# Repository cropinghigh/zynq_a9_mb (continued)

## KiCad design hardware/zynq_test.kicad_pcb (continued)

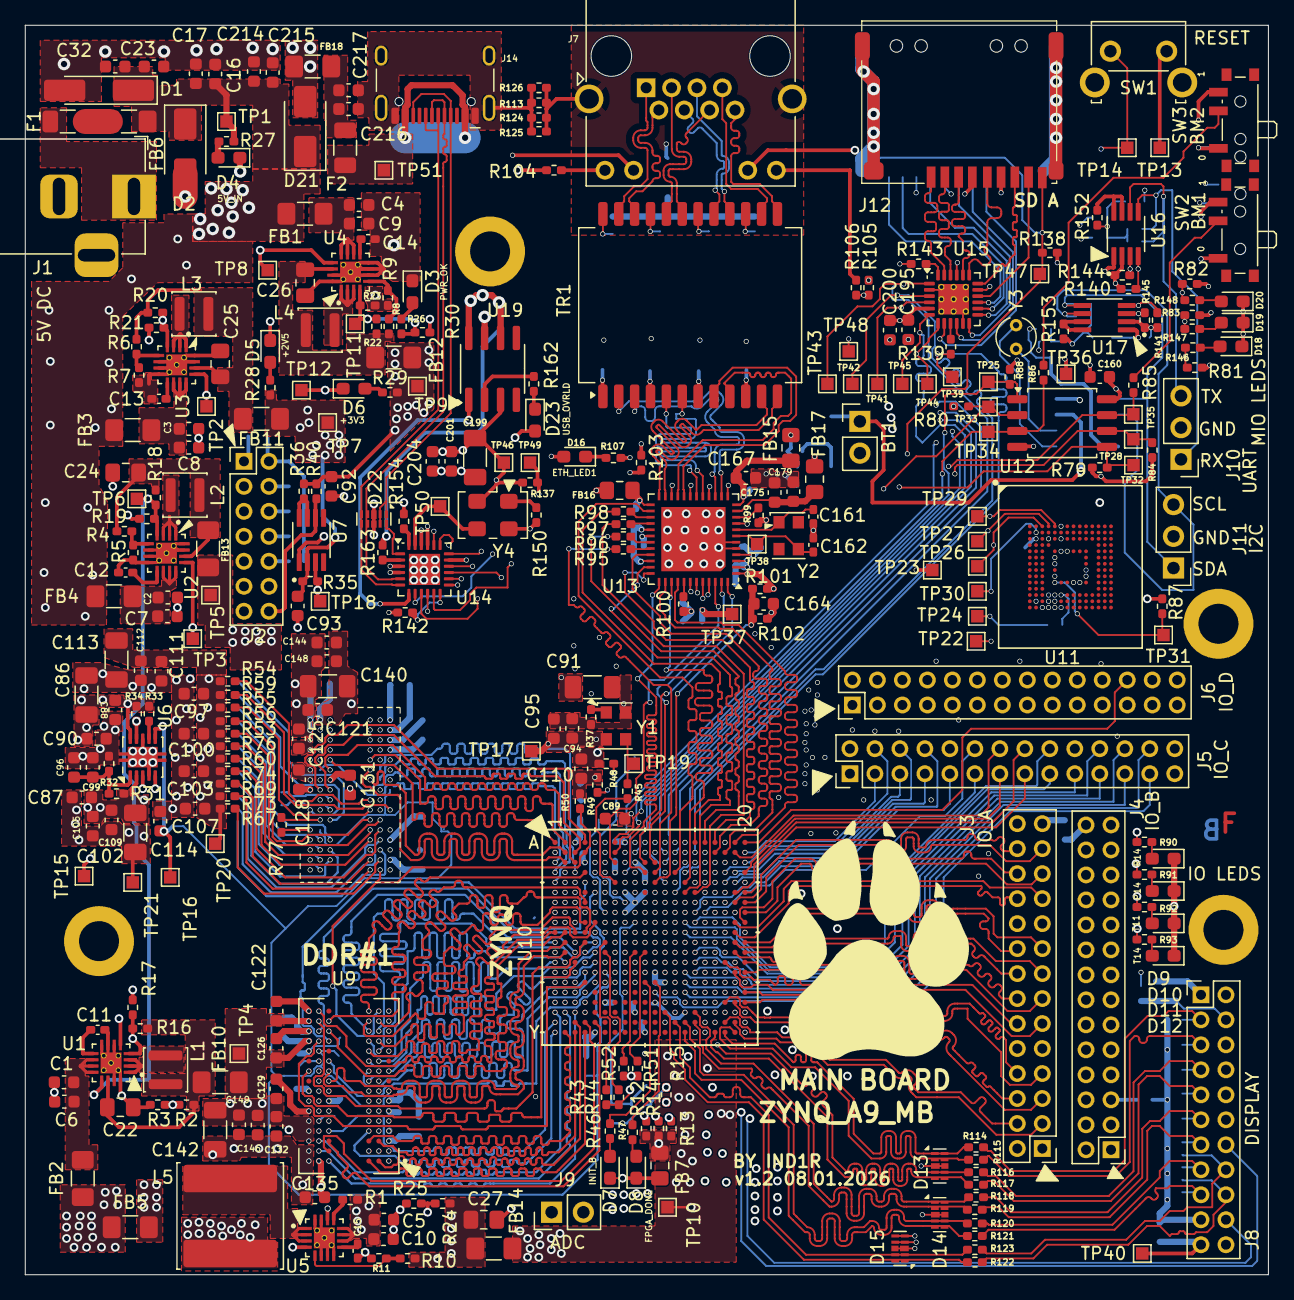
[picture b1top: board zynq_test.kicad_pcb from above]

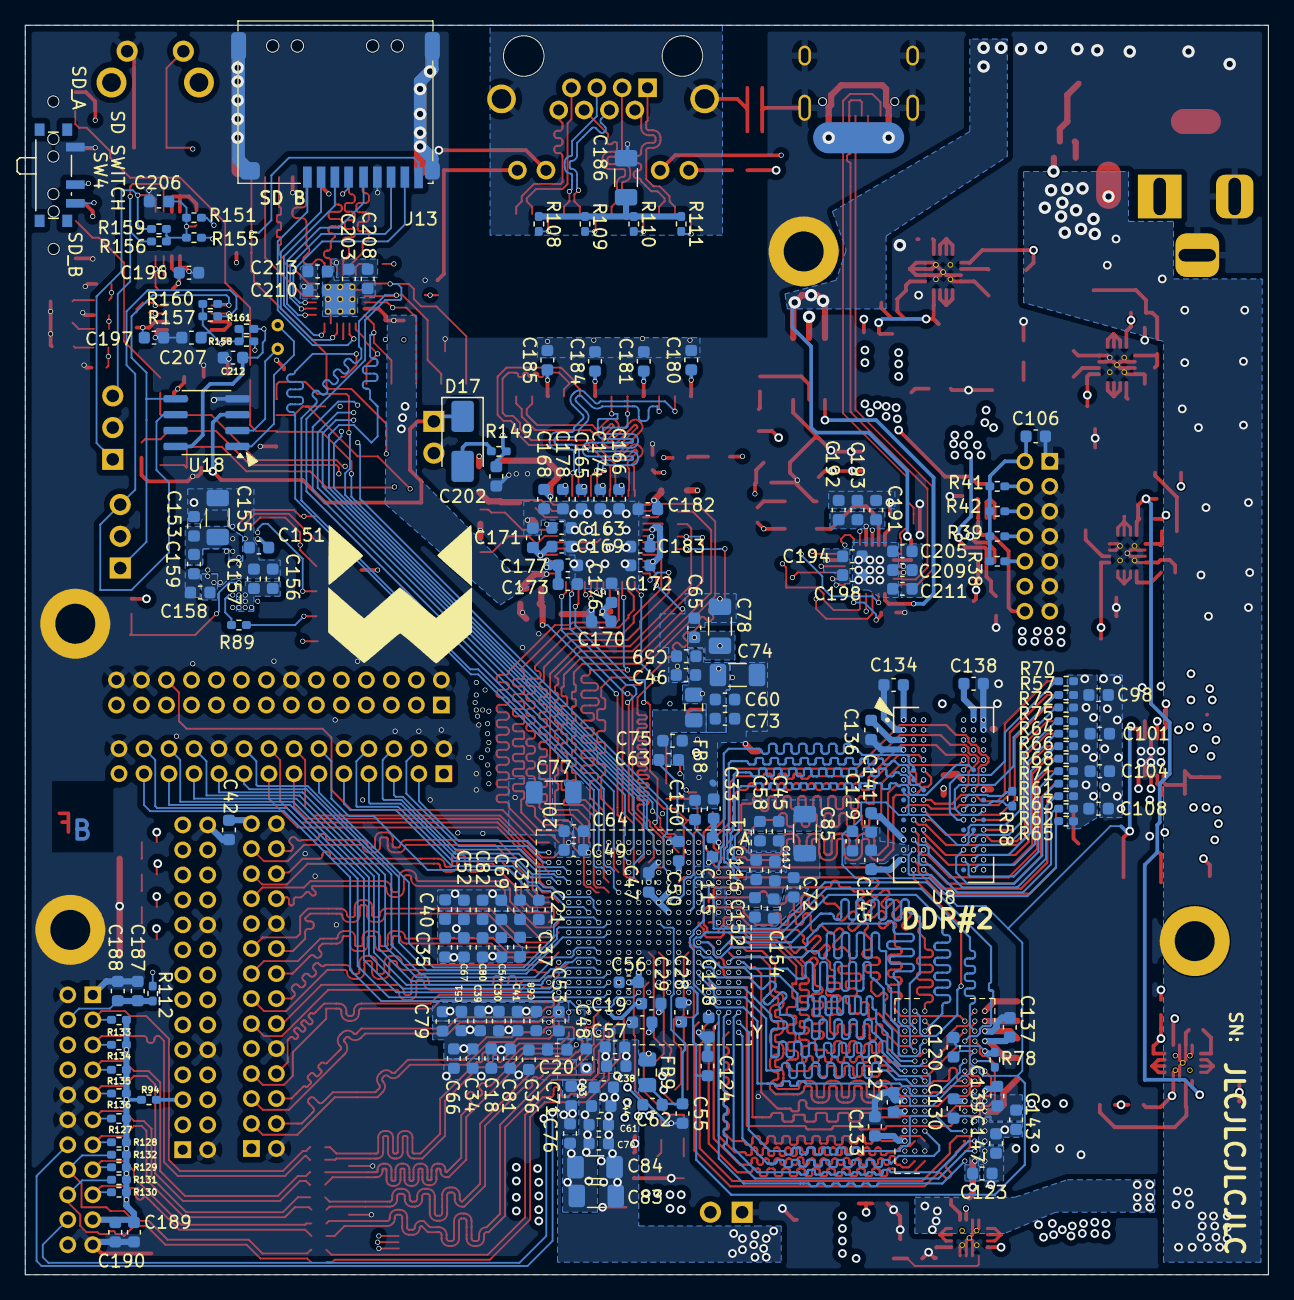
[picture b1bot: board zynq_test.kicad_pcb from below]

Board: 6 copper layers, 99.5 x 100.0 mm, 526 parts (189 on the bottom side), 412 nets.

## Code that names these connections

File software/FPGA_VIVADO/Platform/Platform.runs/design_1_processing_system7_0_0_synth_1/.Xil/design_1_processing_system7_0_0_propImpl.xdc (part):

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set_property src_info {type:SCOPED_XDC file:1 line:410 export:INPUT save:INPUT read:READ} [current_design]
set_property PACKAGE_PIN "E6" [get_ports "MIO[0]"]
set_property src_info {type:SCOPED_XDC file:1 line:415 export:INPUT save:INPUT read:READ} [current_design]
set_property PACKAGE_PIN "H5" [get_ports "DDR_VRP"]
set_property src_info {type:SCOPED_XDC file:1 line:419 export:INPUT save:INPUT read:READ} [current_design]
set_property PACKAGE_PIN "G5" [get_ports "DDR_VRN"]
set_property src_info {type:SCOPED_XDC file:1 line:423 export:INPUT save:INPUT read:READ} [current_design]
set_property PACKAGE_PIN "M5" [get_ports "DDR_WEB"]
set_property src_info {type:SCOPED_XDC file:1 line:427 export:INPUT save:INPUT read:READ} [current_design]
set_property PACKAGE_PIN "P4" [get_ports "DDR_RAS_n"]
set_property src_info {type:SCOPED_XDC file:1 line:431 export:INPUT save:INPUT read:READ} [current_design]
set_property PACKAGE_PIN "N5" [get_ports "DDR_ODT"]
set_property src_info {type:SCOPED_XDC file:1 line:435 export:INPUT save:INPUT read:READ} [current_design]
set_property PACKAGE_PIN "B4" [get_ports "DDR_DRSTB"]
set_property src_info {type:SCOPED_XDC file:1 line:439 export:INPUT save:INPUT read:READ} [current_design]
set_property PACKAGE_PIN "W5" [get_ports "DDR_DQS[3]"]
set_property src_info {type:SCOPED_XDC file:1 line:443 export:INPUT save:INPUT read:READ} [current_design]
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set_property src_info {type:SCOPED_XDC file:1 line:615 export:INPUT save:INPUT read:READ} [current_design]
set_property PACKAGE_PIN "N1" [get_ports "DDR_CS_n"]
set_property src_info {type:SCOPED_XDC file:1 line:619 export:INPUT save:INPUT read:READ} [current_design]
set_property PACKAGE_PIN "N3" [get_ports "DDR_CKE"]
set_property src_info {type:SCOPED_XDC file:1 line:623 export:INPUT save:INPUT read:READ} [current_design]
set_property PACKAGE_PIN "L2" [get_ports "DDR_Clk"]
set_property src_info {type:SCOPED_XDC file:1 line:627 export:INPUT save:INPUT read:READ} [current_design]
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
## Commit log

2025-09-22 add readme
2026-01-08 upload software&build instructions
2026-01-08 Update to v1.2 board&update readme
2026-01-08 update pdf schematic
2026-01-08 update render images
2026-01-08 forgot to update revision on pcb
2026-01-26 upload building and flashing instructions
2026-01-26 Add russian readme
